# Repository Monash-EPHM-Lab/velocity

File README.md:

# velocity
Repository for Monash BoSL In water velocity sensor

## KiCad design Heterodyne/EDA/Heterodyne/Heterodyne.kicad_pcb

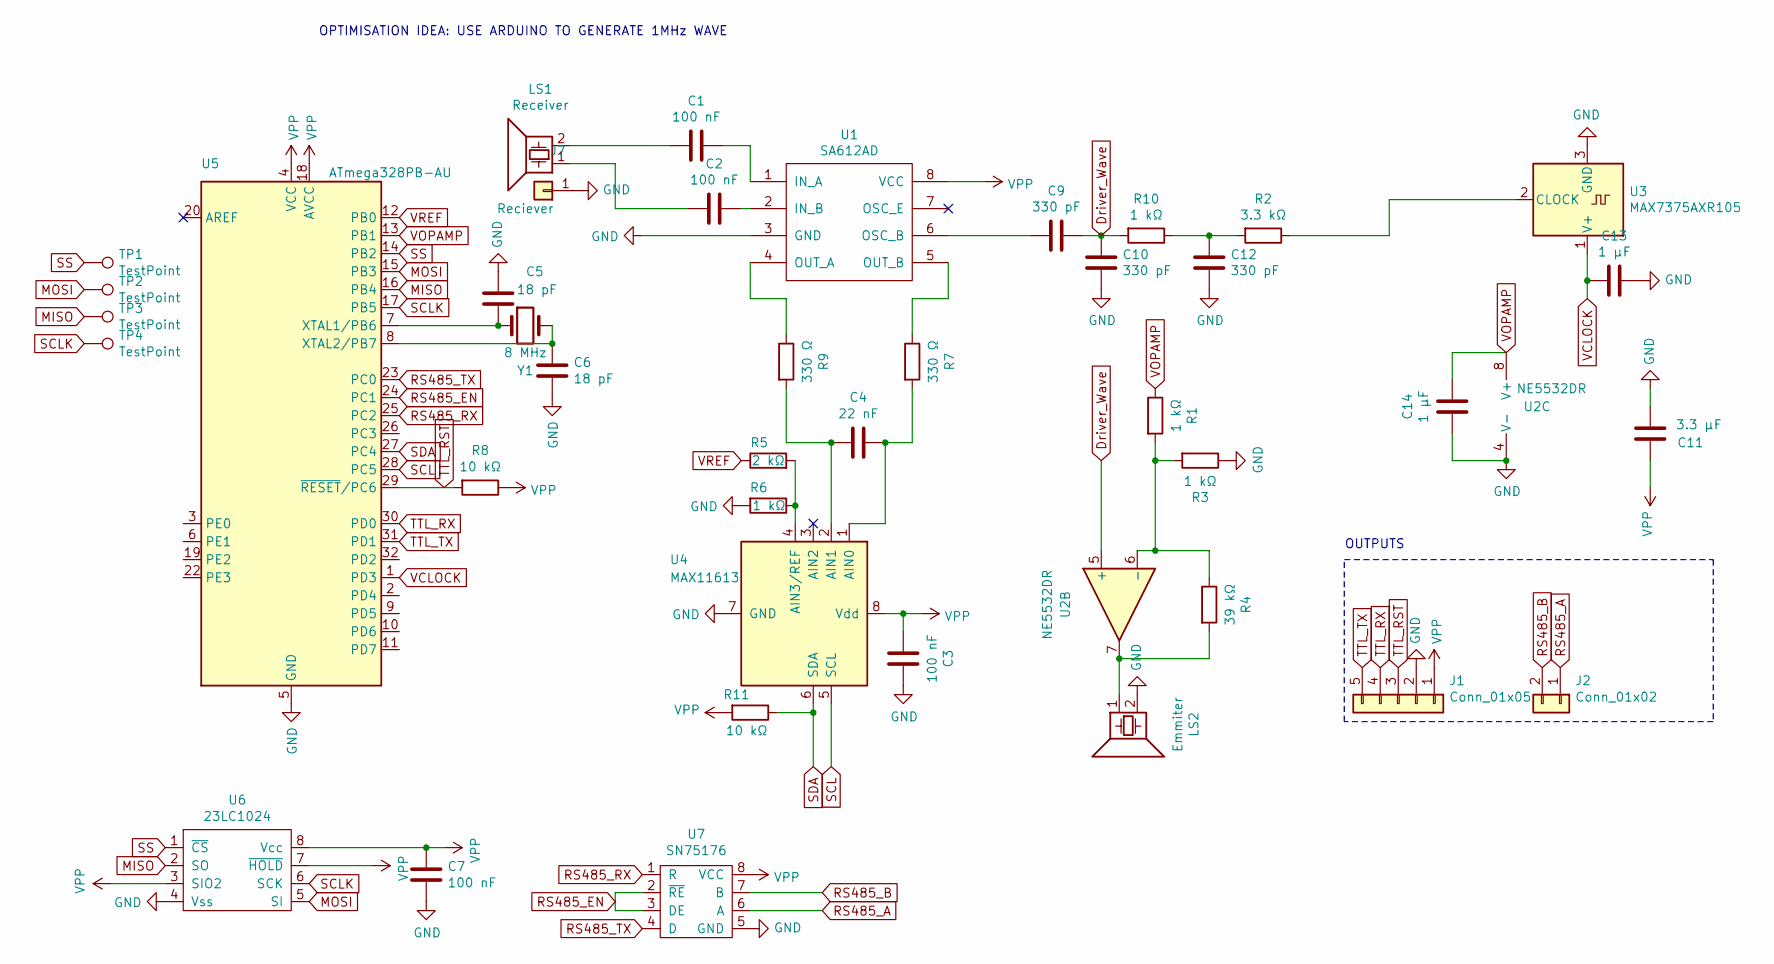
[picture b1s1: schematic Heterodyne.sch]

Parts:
C1, C2, C3, C7: 100 nF; C_0603_1608Metric_Pad1.05x0.95mm_HandSolder
C4: 22 nF; C_0603_1608Metric_Pad1.05x0.95mm_HandSolder
C5, C6: 18 pF; C_0603_1608Metric_Pad1.05x0.95mm_HandSolder
C9, C10, C12: 330 pF; C_0603_1608Metric_Pad1.05x0.95mm_HandSolder
C11: 3.3 μF; C_0805_2012Metric
C13, C14: 1 μF; C_0805_2012Metric
J1: Conn_01x05; PinHeader_1x05_P2.54mm_Vertical
J2: Conn_01x02; PinHeader_1x02_P2.54mm_Vertical
J7: Reciever; PinSocket_1x01_P2.54mm_Vertical
LS1: Receiver; PinHeader_1x02_P2.54mm_Vertical
LS2: Emmiter; PinHeader_1x02_P2.54mm_Vertical
R1, R3, R6, R10: 1 kΩ; R_0603_1608Metric_Pad1.05x0.95mm_HandSolder
R2: 3.3 kΩ; R_0603_1608Metric_Pad1.05x0.95mm_HandSolder
R4: 39 kΩ; R_0603_1608Metric_Pad1.05x0.95mm_HandSolder
R5: 2 kΩ; R_0603_1608Metric_Pad1.05x0.95mm_HandSolder
R7, R9: 330 Ω; R_0603_1608Metric_Pad1.05x0.95mm_HandSolder
R8, R11: 10 kΩ; R_0603_1608Metric_Pad1.05x0.95mm_HandSolder
TP1, TP2, TP3, TP4: TestPoint; Testpoint SPI
U1: SA612AD; SOIC-8_5.275x5.275mm_P1.27mm
U2: NE5532DR; SOIC-8_3.9x4.9mm_P1.27mm
U3: MAX7375AXR105; SOT-323_SC-70_Handsoldering
U4: MAX11613; MSOP-8_3x3mm_P0.65mm
U5: ATmega328PB-AU; TQFP-32_7x7mm_P0.8mm
U6: 23LC1024; SOIC-8_3.9x4.9mm_P1.27mm
U7: SN75176; SOIC-8_3.9x4.9mm_P1.27mm
Y1: 8 MHz; Crystal_SMD_5032-2Pin_5.0x3.2mm

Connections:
Driver_Wave: C9.1, C10.2, R10.2, U2.5 (+)
GND: C3.1, C5.1, C6.2, C7.2, C10.1, C11.2, C12.2, C13.1, C14.2, J1.2, J7.1, LS2.2, R3.1, R6.2, U1.3 (GND), U2.4 (V-), U3.3 (GND), U4.7 (GND), U5.5 (GND), U5.21 (GND), U6.4 (Vss), U7.5 (GND)
MISO: TP3.1, U5.16 (PB4), U6.2 (SO)
MOSI: TP2.1, U5.15 (PB3), U6.5 (SI)
unnamed: C1.1, U1.1 (IN_A)
unnamed: C1.2, LS1.2
unnamed: C2.1, U1.2 (IN_B)
unnamed: C2.2, LS1.1
unnamed: C4.1, R7.2, U4.1 (AIN0)
unnamed: C4.2, R9.2, U4.2 (AIN1)
unnamed: C5.2, U5.7 (XTAL1/PB6), Y1.1
unnamed: C6.1, U5.8 (XTAL2/PB7), Y1.2
unnamed: C9.2, U1.6 (OSC_B)
unnamed: C12.1, R2.2, R10.1
unnamed: LS2.1, R4.2, U2.7
unnamed: R1.2, R3.2, R4.1, U2.6 (-)
unnamed: R2.1, U3.2 (CLOCK)
unnamed: R5.2, R6.1, U4.4 (AIN3/REF)
unnamed: R7.1, U1.5 (OUT_B)
unnamed: R9.1, U1.4 (OUT_A)
RS485_A: J2.1, U7.6 (A)
RS485_B: J2.2, U7.7 (B)
RS485_EN: U5.24 (PC1), U7.2 (~RE), U7.3 (DE)
RS485_RX: U5.25 (PC2), U7.1 (R)
RS485_TX: U5.23 (PC0), U7.4 (D)
SCL: U4.5 (SCL), U5.28 (PC5)
SCLK: TP4.1, U5.17 (PB5), U6.6 (SCK)
SDA: R11.1, U4.6 (SDA), U5.27 (PC4)
SS: TP1.1, U5.14 (PB2), U6.1 (~CS)
TTL_RST: J1.3, R8.2, U5.29 (~RESET~/PC6)
TTL_RX: J1.4, U5.30 (PD0)
TTL_TX: J1.5, U5.31 (PD1)
VCLOCK: C13.2, U3.1 (V+), U5.1 (PD3)
VOPAMP: C14.1, R1.1, U2.8 (V+), U5.13 (PB1)
VPP: C3.2, C7.1, C11.1, J1.1, R8.1, R11.2, U1.8 (VCC), U4.8 (Vdd), U5.4 (VCC), U5.18 (AVCC), U6.3 (SIO2), U6.7 (~HOLD), U6.8 (Vcc), U7.8 (VCC)
VREF: R5.1, U5.12 (PB0)

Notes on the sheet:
OUTPUTS
OPTIMISATION IDEA: USE ARDUINO TO GENERATE 1MHz WAVE

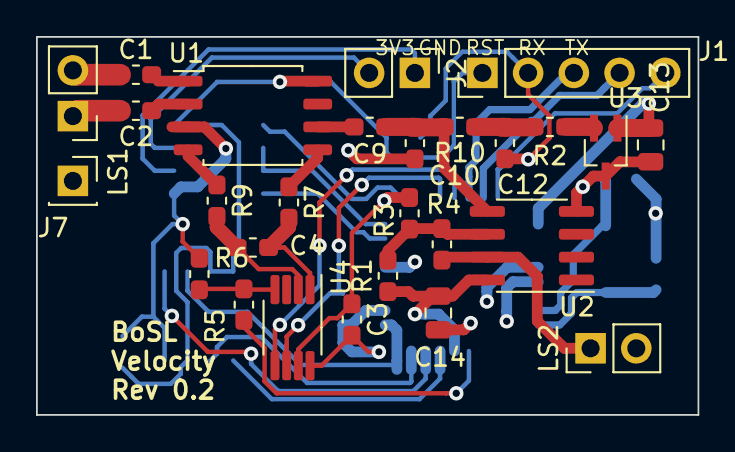
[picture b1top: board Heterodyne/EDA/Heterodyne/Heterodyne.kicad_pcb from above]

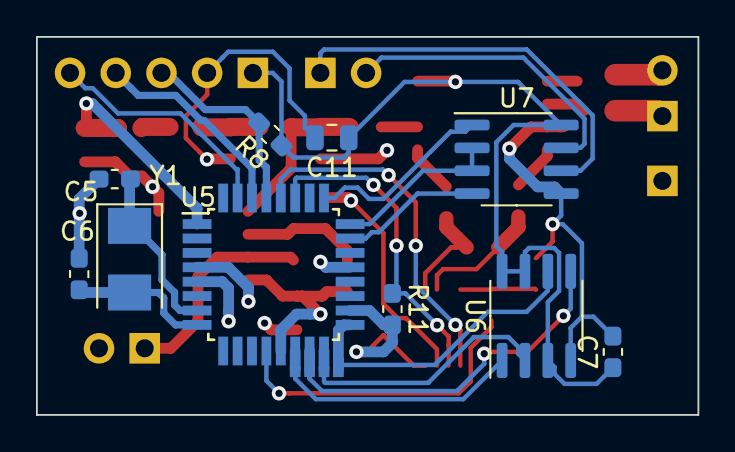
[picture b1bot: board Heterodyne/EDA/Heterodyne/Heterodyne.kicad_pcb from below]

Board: 4 copper layers, 36.8 x 21.0 mm, 41 parts (14 on the bottom side), 36 nets.

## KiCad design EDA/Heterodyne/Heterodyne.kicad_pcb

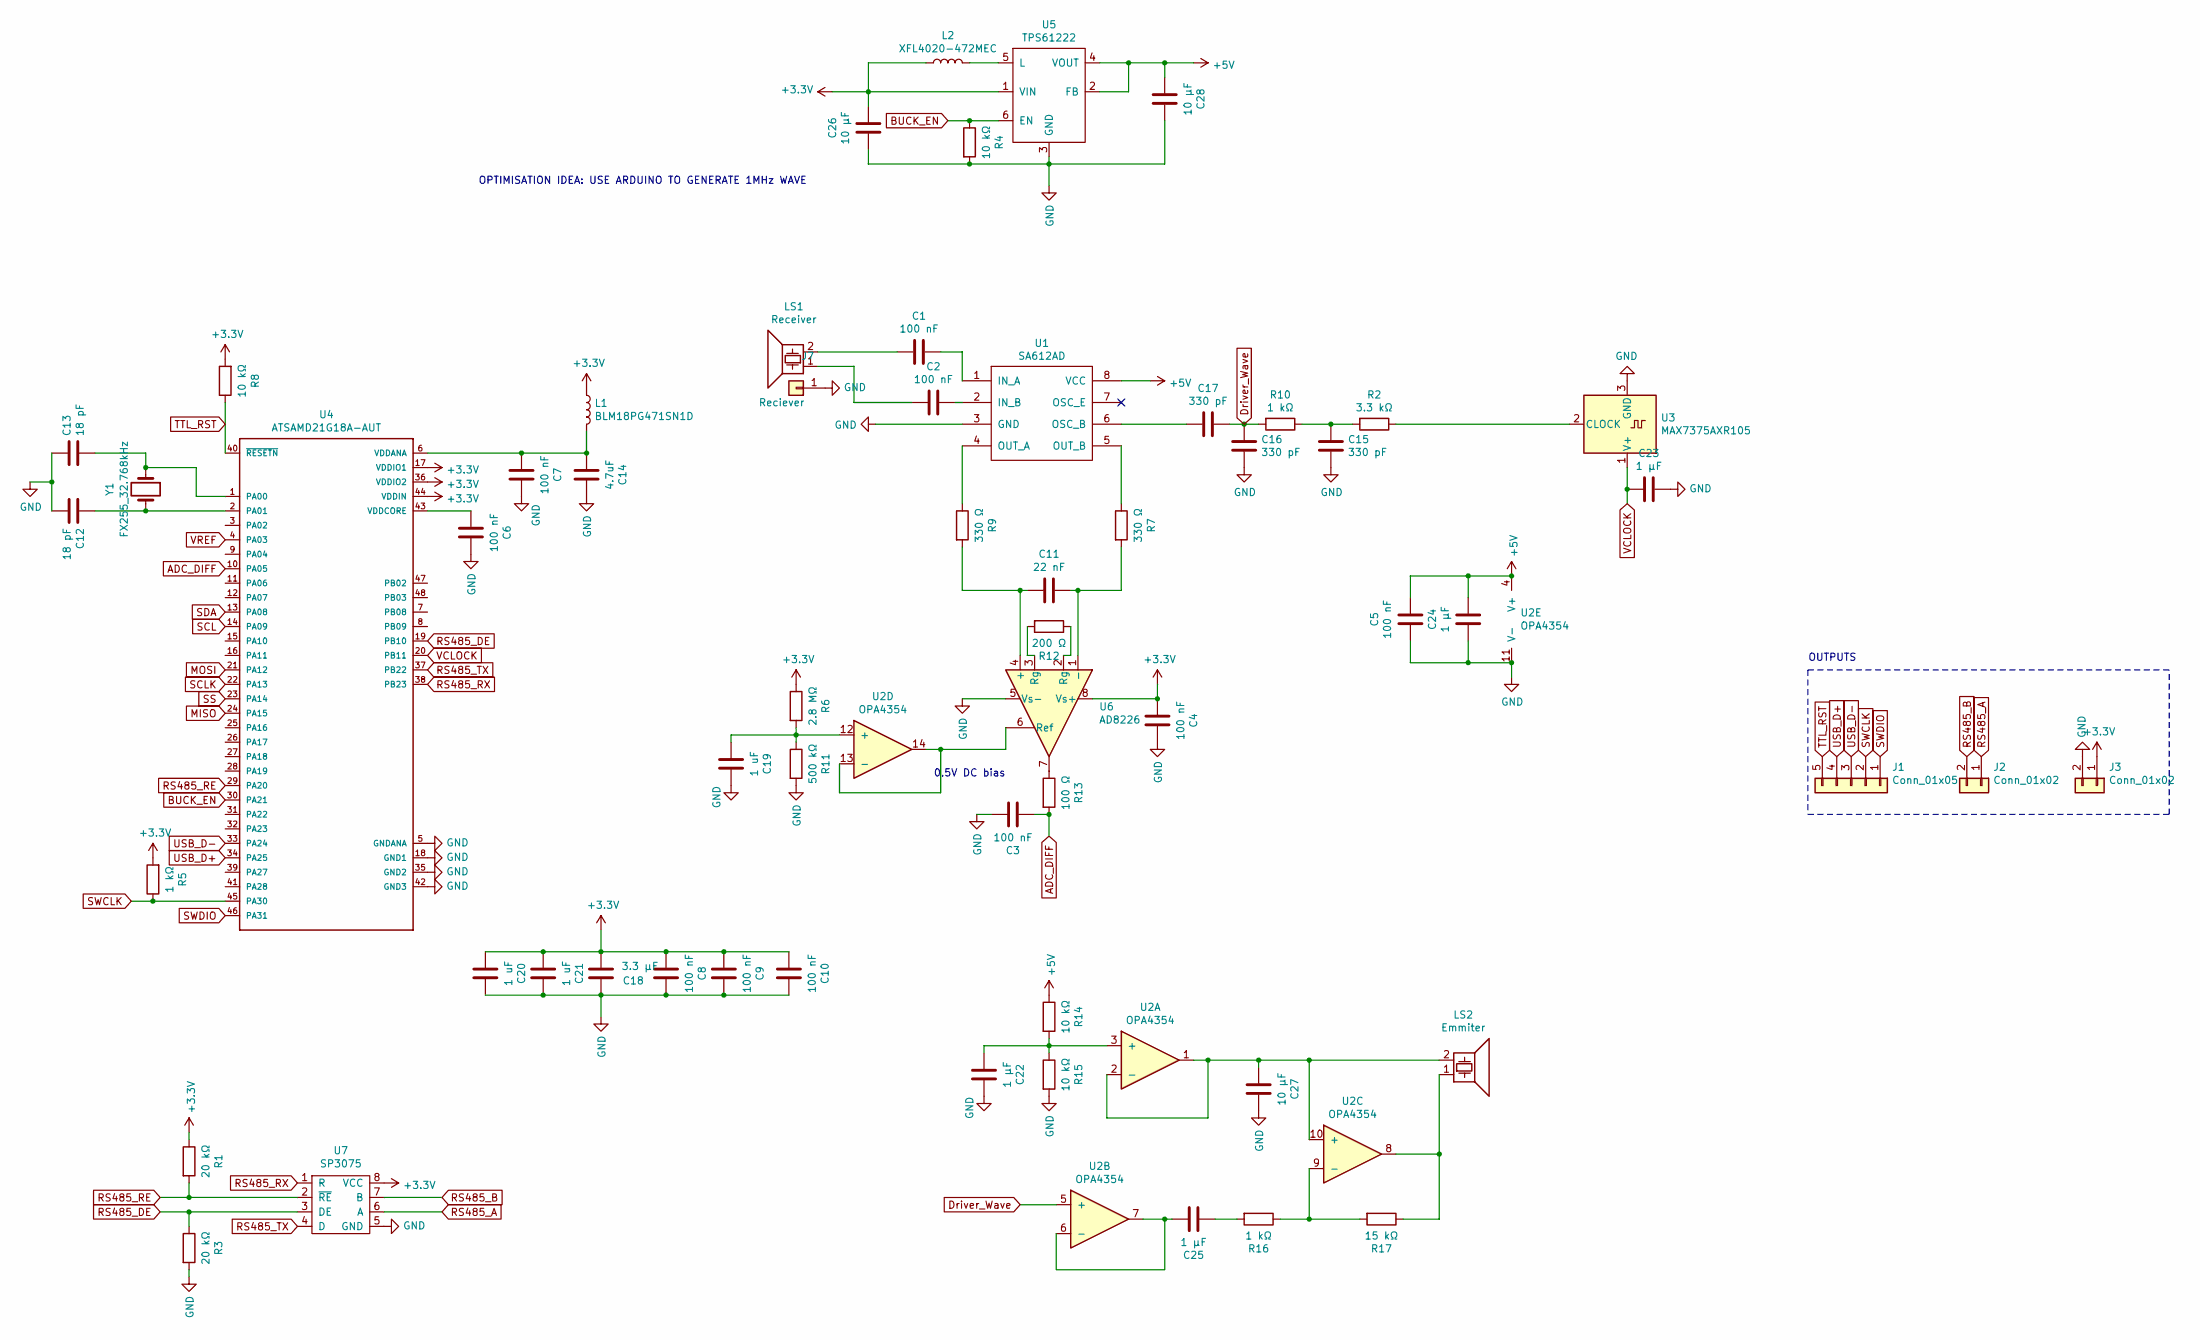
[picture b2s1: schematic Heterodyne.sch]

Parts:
C1, C2, C3, C4, C5: 100 nF; C_0603_1608Metric_Pad1.05x0.95mm_HandSolder
C6, C7, C8, C9, C10: 100 nF; C_0402_1005Metric
C11: 22 nF; C_0603_1608Metric_Pad1.05x0.95mm_HandSolder
C12, C13: 18 pF; C_0603_1608Metric_Pad1.05x0.95mm_HandSolder
C14: 4.7uF; C_0603_1608Metric
C15, C16, C17: 330 pF; C_0603_1608Metric_Pad1.05x0.95mm_HandSolder
C18: 3.3 μF; C_0805_2012Metric
C19, C20, C21: 1 uF; C_0603_1608Metric_Pad1.05x0.95mm_HandSolder
C22: 1 μF; C_0603_1608Metric_Pad1.05x0.95mm_HandSolder
C23, C24, C25: 1 μF; C_0603_1608Metric
C26, C27, C28: 10 μF; C_0805_2012Metric
J1: Conn_01x05; PinHeader_1x05_P2.54mm_Vertical
J2, J3: Conn_01x02; PinHeader_1x02_P2.54mm_Vertical
J7: Reciever; PinSocket_1x01_P2.54mm_Vertical
L1: BLM18PG471SN1D; C_0603_1608Metric
L2: XFL4020-472MEC; L_Coilcraft_XxL4020
LS1: Receiver; PinHeader_1x02_P2.54mm_Vertical
LS2: Emmiter; PinHeader_1x02_P2.54mm_Vertical
R1, R3: 20 kΩ; R_0603_1608Metric_Pad1.05x0.95mm_HandSolder
R2: 3.3 kΩ; R_0603_1608Metric_Pad1.05x0.95mm_HandSolder
R4, R8, R14, R15: 10 kΩ; R_0603_1608Metric_Pad1.05x0.95mm_HandSolder
R5: 1 kΩ; R_0603_1608Metric
R6: 2.8 MΩ; R_0603_1608Metric_Pad1.05x0.95mm_HandSolder
R7, R9: 330 Ω; R_0603_1608Metric_Pad1.05x0.95mm_HandSolder
R10, R16: 1 kΩ; R_0603_1608Metric_Pad1.05x0.95mm_HandSolder
R11: 500 kΩ; R_0603_1608Metric_Pad1.05x0.95mm_HandSolder
R12: 200 Ω; R_0603_1608Metric_Pad1.05x0.95mm_HandSolder
R13: 100 Ω; R_0603_1608Metric_Pad1.05x0.95mm_HandSolder
R17: 15 kΩ; R_0603_1608Metric_Pad1.05x0.95mm_HandSolder
U1: SA612AD; SOIC-8_5.275x5.275mm_P1.27mm
U2: OPA4354
U3: MAX7375AXR105; SOT-323_SC-70_Handsoldering
U4: ATSAMD21G18A-AUT; QFP50P900X900X120-48N
U5: TPS61222; SOT-363_SC-70-6
U6: AD8226; SOIC-8_3.9x4.9mm_P1.27mm
U7: SP3075; SOIC-8_3.9x4.9mm_P1.27mm
Y1: FX255_32.768kHz; Crystal_SMD_MicroCrystal_CC4V-T1A-2Pin_5.0x1.9mm

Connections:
+3V3: C4.2, C8.2, C9.2, C10.2, C18.2, C20.2, C21.2, C26.1, J3.1, L1.1, L2.1, R1.1, R5.2, R6.1, R8.2, U4.17 (VDDIO1), U4.36 (VDDIO2), U4.44 (VDDIN), U5.1 (VIN), U6.8 (Vs+), U7.8 (VCC)
+5V: C5.1, C24.1, C28.2, R14.1, U1.8 (VCC), U2.4 (V+), U5.2 (FB), U5.4 (VOUT); also elsewhere on the board
ADC_DIFF: C3.2, R13.2, U4.10 (PA05)
BUCK_EN: R4.1, U4.30 (PA21), U5.6 (EN)
Driver_Wave: C16.2, C17.1, R10.2, U2.5 (+)
GND: C3.1, C4.1, C5.2, C6.1, C7.1, C8.1, C9.1, C10.1, C12.2, C13.1, C14.1, C15.2, C16.1, C18.1, C19.1, C20.1, C21.1, C22.1, C23.1, C24.2, C26.2, C27.1, C28.1, J3.2, J7.1, R3.2, R4.2, R11.2, R15.2, U1.3 (GND), U2.11 (V-), U3.3 (GND), U4.5 (GNDANA), U4.18 (GND1), U4.35 (GND2), U4.42 (GND3), U5.3 (GND), U6.5 (Vs-), U7.5 (GND); also elsewhere on the board
MISO: U4.24 (PA15)
MOSI: U4.21 (PA12)
unnamed: C1.1, U1.1 (IN_A)
unnamed: C1.2, LS1.2
unnamed: C2.1, U1.2 (IN_B)
unnamed: C2.2, LS1.1
unnamed: C6.2, U4.43 (VDDCORE)
unnamed: C11.1, R7.2, U6.1 (-)
unnamed: C11.2, R9.2, U6.4 (+)
unnamed: C12.1, U4.2 (PA01), Y1.2
unnamed: C13.2, U4.1 (PA00), Y1.1
unnamed: C7.2, C14.2, L1.2, U4.6 (VDDANA)
unnamed: C15.1, R2.2, R10.1
unnamed: C17.2, U1.6 (OSC_B)
unnamed: C19.2, R6.2, R11.1, U2.12 (+)
unnamed: C22.2, R14.2, R15.1, U2.3 (+)
unnamed: C25.1, U2.6 (-), U2.7
unnamed: C25.2, R16.2
unnamed: C27.2, LS2.2, U2.1, U2.2 (-), U2.10 (+)
unnamed: L2.2, U5.5 (L)
unnamed: LS2.1, R17.1, U2.8
unnamed: R2.1, U3.2 (CLOCK)
unnamed: R7.1, U1.5 (OUT_B)
unnamed: R9.1, U1.4 (OUT_A)
unnamed: R12.1, U6.2 (Rg)
unnamed: R12.2, U6.3 (Rg)
unnamed: R13.1, U6.7
unnamed: R16.1, R17.2, U2.9 (-)
unnamed: U2.13 (-), U2.14, U6.6 (Ref)
RS485_A: J2.1, U7.6 (A)
RS485_B: J2.2, U7.7 (B)
RS485_DE: R3.1, U4.19 (PB10), U7.3 (DE)
RS485_RE: R1.2, U4.29 (PA20), U7.2 (~RE)
RS485_RX: U4.38 (PB23), U7.1 (R)
RS485_TX: U4.37 (PB22), U7.4 (D)
SCL: U4.14 (PA09)
SCLK: U4.22 (PA13)
SDA: U4.13 (PA08)
SS: U4.23 (PA14)
SWCLK: J1.2, R5.1, U4.45 (PA30)
SWDIO: J1.1, U4.46 (PA31)
TTL_RST: J1.5, R8.1, U4.40 (~RESETN~)
USB_D+: J1.4, U4.34 (PA25)
USB_D-: J1.3, U4.33 (PA24)
VCLOCK: C23.2, U3.1 (V+), U4.20 (PB11)
VREF: U4.4 (PA03)

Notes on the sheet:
OUTPUTS
OPTIMISATION IDEA: USE ARDUINO TO GENERATE 1MHz WAVE
0.5V DC bias

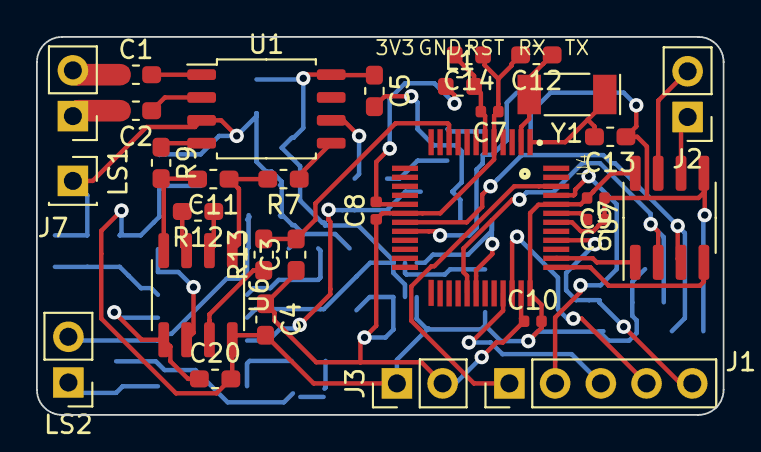
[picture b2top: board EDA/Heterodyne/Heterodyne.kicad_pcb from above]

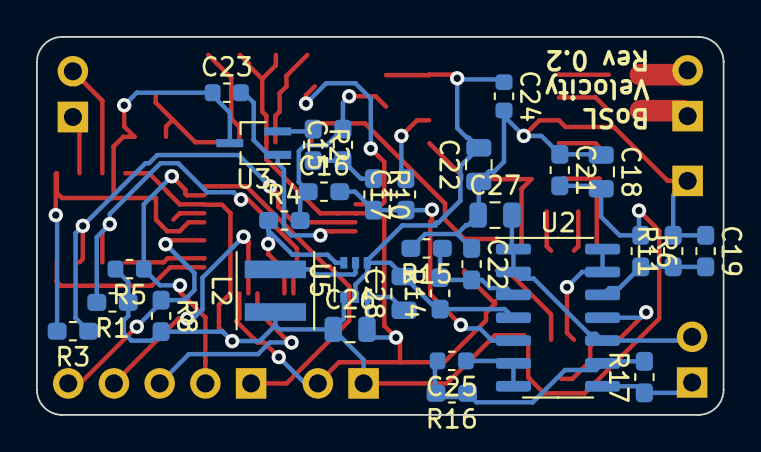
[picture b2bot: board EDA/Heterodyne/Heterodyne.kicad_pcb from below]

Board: 4 copper layers, 38.2 x 21.0 mm, 62 parts (31 on the bottom side), 45 nets.

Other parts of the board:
C22#2: 2.2 μF; C_0805_2012Metric

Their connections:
+5V: C22#2.2; also elsewhere on the board
GND: C22#2.1; also elsewhere on the board

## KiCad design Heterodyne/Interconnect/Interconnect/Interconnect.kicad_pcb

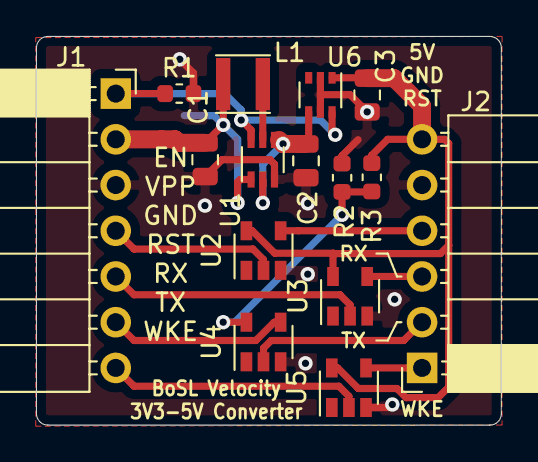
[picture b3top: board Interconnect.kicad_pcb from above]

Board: 2 copper layers, 25.8 x 21.6 mm, 16 parts (1 on the bottom side), 15 nets.

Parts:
C1, C2: 10 μF; C_0805_2012Metric
C3: 1 μF; C_0805_2012Metric
J1: Conn_01x07; PinSocket_1x07_P2.54mm_Horizontal
J2: Conn_01x06; PinSocket_1x06_P2.54mm_Horizontal
JP1: SolderJumper_2_Open; SolderJumper-2_P1.3mm_Open_Pad1.0x1.5mm
L1: NR3015T4R7M; L_Taiyo-Yuden_NR-30xx
R1: 10 kΩ; R_0603_1608Metric
R2: 1.5 kΩ; R_0603_1608Metric
R3: 680 Ω; R_0603_1608Metric
U1: TPS61222DCK; Texas_R-PDSO-G6
U2, U3, U4, U5: SN74LV1T34DBVR; SOT-23-5
U6: MIC94090; SOT-363_SC-70-6

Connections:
+3V3: R2.1, R3.2, U4.5
+5V: C3.1, J2.6, R3.1, U2.5, U3.5, U5.5, U6.1
EN: J1.1, JP1.1, R1.1, U1.6, U6.6
GND: C1.2, C2.2, C3.2, J1.3, J2.5, R1.2, R2.2, U1.3, U2.3, U3.3, U4.3, U5.3, U6.2, U6.5
unnamed: C2.1, U1.2, U1.4, U6.4
unnamed: J1.4, U2.2
unnamed: J1.5, U3.2
unnamed: J1.6, U4.4
unnamed: J1.7, U5.2
unnamed: J2.1, U5.4
unnamed: J2.2, U4.2
unnamed: J2.3, U3.4
unnamed: J2.4, U2.4
unnamed: L1.2, U1.5
VPP: C1.1, J1.2, JP1.2, L1.1, U1.1

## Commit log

2020-08-11 initial commit for split of monash-bosl repo into component projects
2020-08-11 reorganised files
2020-08-11 initial commit of SAMD21 branch
2020-08-27 fixed temprature on case print
2020-09-08 tweaked velocity algorithm
2020-09-08 deleted temp files
2020-09-10 added production version of velocity firmware for testing
2020-09-17 added PSD for 3 velocity sensors
2020-09-18 added untested unified library
2020-09-18 checked working RS485 library
2020-09-29 added calibration data for sensors
2020-10-04 added stat analysis
2020-10-05 added new data
2020-10-11 added mean to error analysis
2020-10-12 added for code for ID012
2020-10-18 -added delay for analog components starting up -added new week of data
2020-10-25 added week 11 data
2020-11-01 about to change edge detection function
2020-11-01 semi-working canny filter
2020-11-19 v good velocity algorithm
2020-11-20 final velocity algorithm
2020-11-23 pretty images and plots
2020-11-25 addded data export function
2020-11-26 updated code for ease of use
2020-12-01 added test for the final algorithm implementation in arduino code
2021-02-01 minor update to firmware
